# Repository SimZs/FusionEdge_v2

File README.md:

# FusionEdge V2.0

ESP32-S3 alapú internetes rádió, helyi és hálózati lejátszással, valamint kétirányú Bluetooth-audióval. Aktuális kiadás: **v2.0.4**.

Ez a FusionEdge továbbfejlesztett, PlatformIO/Arduino-alapú firmware-e.

## Mi változott a 2.0.4-ben?

- Stabilabb HTTPS-rádiólejátszás: az ESP32-S3 nagy TLS-pufferei PSRAM-ba kerülnek, a WebUI tömörített alaperőforrásai pedig PSRAM-ból szolgálhatók ki. Ez mérsékli a belső memória terhelését a beállítások megnyitásakor és borítókép-letöltés közben.
- Az audiofeladat a lefoglalt verem teljes méretét használja, így a TLS-es újracsatlakozás nem fut bele a korábbi veremőrző hibába.
- Az óránkénti, `:00` perckor elnémuló TTS javítva; a képernyővédő órájának másodpercei frissülnek.
- Nyitott hangszínszabályzóra nem lép rá az automatikus képernyővédő. Bezárás után újraindul az időzítése.

Ha már a 2.0.3 LittleFS-adatállománya van a készüléken, ehhez a kiadáshoz elég a firmware-t frissíteni; teljes törlés nem szükséges. A kiadás forráskódot tartalmaz, előre fordított firmware-t és személyes konfigurációt nem.

## Mi változott a 2.0.3-ban?

- A WebUI lejátszási listájában ismét működik az állomásnév szerinti keresés; a műfajok közül is lehet választani és műfajra szűrni.
- A Wi-Fi a scanben név nélkül megjelenő, rejtett mentett hálózatokat is megpróbálja elérni. A csatlakozási várakozás hálózatonként 45 másodperc, hogy a lassabban válaszoló vagy gyenge jelű AP miatt ne induljon túl korán AP módba.

A WebUI-javításhoz a firmware mellett a LittleFS-t is frissíteni kell. Full erase nem szükséges. Ha egyik mentett hálózat sem érhető el, az AP módba lépés az eddiginél tovább tarthat.

## Mi változott a 2.0.2-ben?

- Első indításkor a firmware a mentett lejátszási módhoz igazítja az FSC-BT1058 szerepét. A gyári Sink állapotú modul WEB/SD/DLNA módban magától Source módra vált; a WebUI keresőgombja a beállítás és ellenőrzés után kézi oda-vissza módváltás nélkül aktiválódik.
- Bluetooth Input módból indulva az audióhíd megvárja a modul szerepének és I2S-beállításainak ellenőrzését.

## Mi változott a 2.0.1-ben?

- Bluetooth-kimenetnél a párosított hangszórók között közvetlenül lehet váltani. A rádió előbb bontja a meglévő kapcsolatot, majd az újhoz csatlakozik; sikertelen váltás után megpróbálja visszaállítani az előzőt.
- Kijelző- és érintésigazítások az időjárás és a Bluetooth-eszközlista körül.
- Javítottuk a DLNA-worker fordítási figyelmeztetését.
- A [hardware mappába](hardware/README.md) bekerült az FSC-BT1058 adapter kapcsolási rajza, NYÁK-terve és gyártási csomagja.

## Mi új a 2.0.0-ban?

- Az FSC-BT1058 modul Bluetooth-bemenetként és -kimenetként is használható, a két szerep között váltva. Bemenetként telefonról vagy PC-ről fogad hangot; kimenetként a rádió hangja párosított Bluetooth-hangszóróra küldhető. Az elérhető kodek a kapcsolódó eszköztől és a modul firmware-étől függ.
- Átalakult a 480×320-as lejátszóképernyő: nagyobb állomáslogó/borító, külön előző–lejátszás/szünet–következő gombok, szöveges audióinformáció, külön mód- és csatornaszám-mező, valamint új információs nézetek.
- A beállítások, a képernyővédő-választás és több korábbi főképernyős kapcsoló egy közös kijelzőmenübe került. Érintőképernyő nélkül, enkóderrel is kezelhető.
- A WebUI önálló Bluetooth-részt kapott. A Last.fm borítókeresés engedélyezése és API-kulcsa, valamint a lejátszás közbeni képernyővédő stílusa már a WebUI-ban állítható.
- A mellékelt logótérkép-készítő a rádiólistából állomáslogókat keres, ellenőriz, PNG-re alakít és a LittleFS méretkeretéhez igazítva exportál.
- Opcionális, MQTT-alapú Home Assistant-integráció és saját FusionEdge oldalsávos kezelőoldal készült.

## Érintőképernyő – a 480×320-as elrendezés

| Érintett terület | Művelet |
| --- | --- |
| Metaadat és első címsor | Állomás-presetek megnyitása; a presetnézet fejlécével lehet visszalépni. |
| Bal felső állomáslogó / borító | A nagy coverart-nézet megnyitása; újabb érintéssel vissza a lejátszóhoz. Az automatikus képernyővédő beállítása nem változik. |
| Előző / lejátszás–szünet / következő ikon | Lejátszás vezérlése; Bluetooth-bemenetnél a csatlakozott telefon/PC felé küld vezérlést. |
| Bal alsó Bluetooth-ikon | Kapcsolat és párosított eszközök megtekintése, kapcsolódás/bontás. |
| `MODE` mező | Lejátszási mód választása. |
| Középső menüikon | Kijelzőbeállítások megnyitása. |
| `Ch.:` mező | Aktuális lejátszási lista megnyitása. |
| Jobb alsó Wi-Fi-ikon | SSID, IP-cím és jelerősség. |
| Időjárásikon | Ötnapos előrejelzés. |
| Jobb oldali függőleges hangerőskála | Hangerő állítása érintéssel. |

A korábbi, általános fel/le húzás nem vált módot vagy állomást: a listákban görgetésre szolgál. A kijelzőbeállítások között `MODE`, `FADE`, `TTS`, `RGB`, `VOLUME` és `SCREENSAVER` található. A menü 5 másodperc tétlenség után záródik; egy beállítás megváltoztatása önmagában nem léptet ki.

## Enkóder

A fő lejátszóképernyőn a forgatás hangerőt állít, az egyszeri gombnyomás lejátszás/szünet, a dupla kattintás a kijelzőbeállításokat, a hosszú nyomás a lejátszási listát nyitja meg. Nyitott listában vagy választómenüben a forgatás kijelöl, az egyszeri nyomás megerősít. A dupla és hosszú nyomás nem írja felül a már nyitott Settings, Volume, Wi-Fi, Bluetooth vagy Forecast nézetet. A Wi-Fi-adatok a Settings alsó sorában érintőképernyő nélkül is elérhetők.

## WebUI

- **Bluetooth:** Input oldalon név (alias) és felfedezhetőség; Output oldalon `Bluetooth only`, `Local + Bluetooth` és `Local only`. A csatlakoztatott/párosított eszközök és az új hangszórók keresése külön kezelhető.
- **Extras → Last.fm cover art:** a funkció engedélyezése és a saját, 32 karakteres API-kulcs megadása. Érvényes kulcs nélkül nincs Last.fm-lekérés; a borítókeresés MusicBrainz-forrást is használhat. Az API-kulcsot ne tedd nyilvános repóba.
- **Screens → Screensaver:** a szokásos képernyővédő mellett a lejátszás közbeni működés külön kapcsolható. Stílusok: `CoverArt`, `Cassette`, `Analog VU Meter`.

A helyi állomáslogókhoz lásd a [TuneIn map builder útmutatóját](tools/tunein_map_builder/README.md). A logók letöltése a számítógépen történik; a rádió a LittleFS-re feltöltött PNG-ket használja, nem tölti le a `map.csv` távoli URL-jeit lejátszás közben.

Az állomások egyedi logói nem részei ennek a kiadásnak. **Az első LittleFS-feltöltés előtt a saját vagy a mellékelt `playlist.csv` fájlból készítsd el a kívánt logókat és a hozzájuk tartozó `map.csv` fájlt** a mellékelt segédprogrammal. A `plmodeweb.png`, `plmodesd.png`, `plmodedlna.png` és `plmodebt.png` fallback ikonokat ne töröld: ezek logó nélkül is szükségesek. Ha nem készítesz állomáslogókat, a rádió ezekkel a fallback ikonokkal működik.

## Home Assistant

Az opcionális [Home Assistant-integráció](HA/README.md) MQTT-n keresztül automatikusan felismerhető rádiót, média-lejátszó entitást és FusionEdge oldalsávos kezelőoldalt ad. A Bluetooth-eszközök keresése és párosítása továbbra is a rádió WebUI-jában történik.

## Bluetooth-adapter

Az FSC-BT1058 modulhoz tartozó adapter kapcsolási rajza, NYÁK-terve és gyártási fájljai a [hardware mappában](hardware/README.md) találhatók. Az ottani rövid útmutató a bekötés célját és a modul beszerzési linkjét is tartalmazza.

## Telepítési megjegyzések

A jelenlegi PlatformIO-mintakörnyezet az ESP32-S3 és a 480×320-as ST7796 kijelző használatához készült. Más panelhez a megfelelő, ellenőrzött hardverkonfiguráció szükséges. Feltöltés előtt ellenőrizd, hogy a `myoptions.h` beállításai a saját hardveredhez illenek. A firmware mellett a projekt `data` tartalmát is fel kell tölteni LittleFS-re, különben a WebUI és a képek hiányozhatnak.

Az első feltöltés előtt másold a `data/data/wifi.example.csv` fájlt `data/data/wifi.csv` néven, és írd bele a saját hálózataidat. MQTT/Home Assistant használatához másold a `mqttoptions.example.h` fájlt `mqttoptions.h` néven, majd állítsd be a saját brokeredet; MQTT nélkül ez a fájl nem szükséges. A `wifi.csv` és a `mqttoptions.h` személyes adatokat tartalmazhat, ezért ne töltsd fel őket GitHubra. Feltöltés vagy teljes törlés előtt készíts mentést róluk, valamint a saját beállításaidról és API-kulcsaidról.

A mellékelt `data/data/playlist.csv` használható kiinduló rádiólista, amelyet szabadon lecserélhetsz a sajátodra. Az `ircodes.csv` nem része a kiadásnak: a saját infratávirányító betanítása után a kódokat a rádióból tudod elmenteni.

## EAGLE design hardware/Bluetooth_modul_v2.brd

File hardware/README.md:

# FSC-BT1058 Bluetooth-adapter

A FusionEdge V2.0 kétirányú Bluetooth-audiójához FSC-BT1058 modul kell. Ez a kis adapter-nyák a modul beültetését és a rádióhoz csatlakoztatását egyszerűsíti: egy 8 tűs JST-XH csatlakozóra vezeti ki a 3,3 V-os tápot, az UART-ot és az I²S hangjeleket. A szükséges `SYS_CTRL` bekapcsolóáramkör (2N7002) és a táp szűrőelemei is az adapteren vannak. A `RST` és `SYS_CTRL` külön tesztpadon is elérhető; az `MCLK` nem része a csatlakozónak.

A mappában az Eagle kapcsolási rajz (`.sch`), a NYÁK-terv (`.brd`), a gyártási Gerber- és fúrófájlokat tartalmazó ZIP, valamint az adapter képe található. A csatlakozó bekötését és a beültetendő alkatrészeket mindig a mellékelt kapcsolási rajz alapján ellenőrizd; a modult ne kösd közvetlenül 5 V-ra.

FSC-BT1058 modul: [Feasycom vásárlási oldal az Alibabán](https://www.alibaba.com/product-detail/Feasycom-FSC-BT1058-Qualcomm-QCC5181-Bluetooth_1601272259871.html?spm=a2756.trade-list-buyer.0.0.f34876e92KzOtz).

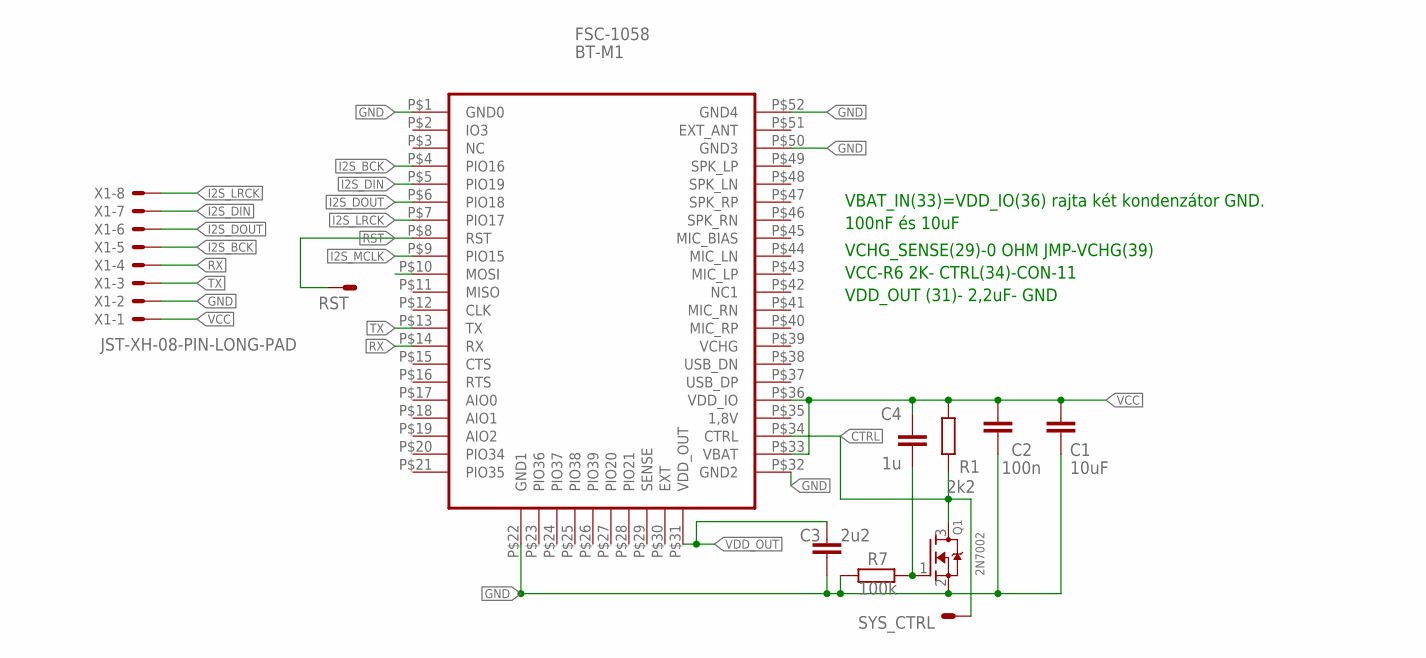
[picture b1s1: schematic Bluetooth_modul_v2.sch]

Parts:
BT-M1: FSC-1058; FSC-1054
C1: 10uF; C0805
C2: 100n; C0603
C3: 2u2; C0603
C4: 1u; C0805
Q1: 2N7002; SOT23
R1: 2k2; R0603
R7: 100k; R0603
RST: PAD1
SYS_CTRL: PAD1
X1: JST-XH-08-PIN-LONG-PAD; JST-XH-08-PACKAGE-LONG-PAD

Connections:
CTRL: BT-M1.P$34 (CTRL), Q1.3 (D), R1.1, SYS_CTRL.1
GND: BT-M1.P$1 (GND0), BT-M1.P$22 (GND1), BT-M1.P$32 (GND2), BT-M1.P$50 (GND3), BT-M1.P$52 (GND4), C1.1, C2.1, C3.1, Q1.2 (S), R7.2, X1.2
I2S_BCK: BT-M1.P$4 (PIO16), X1.5
I2S_DIN: BT-M1.P$5 (PIO19), X1.7
I2S_DOUT: BT-M1.P$6 (PIO18), X1.6
I2S_LRCK: BT-M1.P$7 (PIO17), X1.8
I2S_MCLK: BT-M1.P$9 (PIO15)
unnamed: C4.1, Q1.1 (G), R7.1
RST: BT-M1.P$8 (RST), RST.1
RX: BT-M1.P$14 (RX), X1.4
TX: BT-M1.P$13 (TX), X1.3
VCC: BT-M1.P$33 (VBAT), BT-M1.P$36 (VDD_IO), C1.2, C2.2, C4.2, R1.2, X1.1
VDD_OUT: BT-M1.P$31 (VDD_OUT), C3.2

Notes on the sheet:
VBAT_IN(33)=VDD_IO(36) rajta két kondenzátor GND.
100nF és 10uF
VDD_OUT (31)- 2,2uF- GND
VCHG_SENSE(29)-0 OHM JMP-VCHG(39)
VCC-R6 2K- CTRL(34)-CON-11

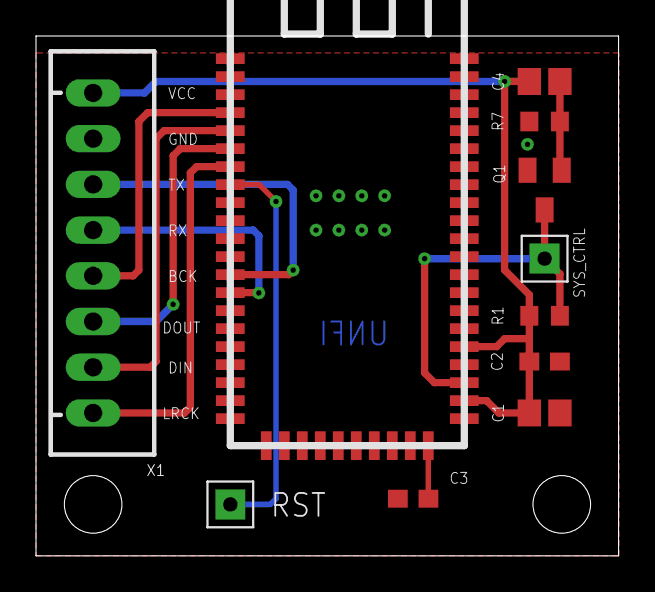
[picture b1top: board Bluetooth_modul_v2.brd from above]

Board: 2 copper layers, 32.4 x 28.9 mm, 11 parts (0 on the bottom side), 12 nets.
